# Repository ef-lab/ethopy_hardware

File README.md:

# 🏠 Hardware for EthoPy

Welcome to the **Hardware for EthoPy** repository! This collection includes all hardware information required to build the setups described in EthoPy. 

## 📦 What's Inside

This repo includes one folder for each behavioral system supported by EthoPy with the:
- **Instructions** – step-by-step guides to build this setup and parts list 
- **Figures** - Photos illustrating the construction process and final setup
- **3d_designs** – ready-to-print `.stl` files 

## 📁 File Structure

```bash
├── Air-track
│   ├── 3d_designs
│   ├── Air-track_instructions.md
│   └── figures
├── EthoPy_Controller
│   ├── Controller_Figures
│   ├── EthoPy_Controller_Board.md
│   ├── EthoPy_Controller_code.ino
│   ├── Lick_Valves_final.jpg
│   ├── Lick_Valves_final.kicad_pcb
│   ├── Valve_Controller.pdf
│   └── gerbers
├── Homecage
│   ├── 3d_designs
│   ├── Lick_ports_Figures
│   ├── Lick_ports_assemply.md
│   ├── RP_Figures
│   ├── RP_instructions.md
│   ├── Speakers_Figures
│   └── Speakers_assemply.md
├── LICENSE
├── Open-field
│   ├── 3d_designs
│   ├── Open-field_Figures
│   └── Open-field_instructions.md
├── README.md
└── Spherical_Treadmill
    ├── 3d_design
    ├── figures
    └── spherical_treadmill_instructions.md
```

<!-- ## 📸 Gallery

_Add screenshots or photos of the final printed setup here!_ -->

## 🛠️ Modifications & Contributions

Want to tweak a design? Feel free to fork the repo and customize. PRs are welcome if you want to contribute new variations or improvements!

## 📜 License

This project is licensed under the **MIT License** – see the [LICENSE](./LICENSE) file for details.

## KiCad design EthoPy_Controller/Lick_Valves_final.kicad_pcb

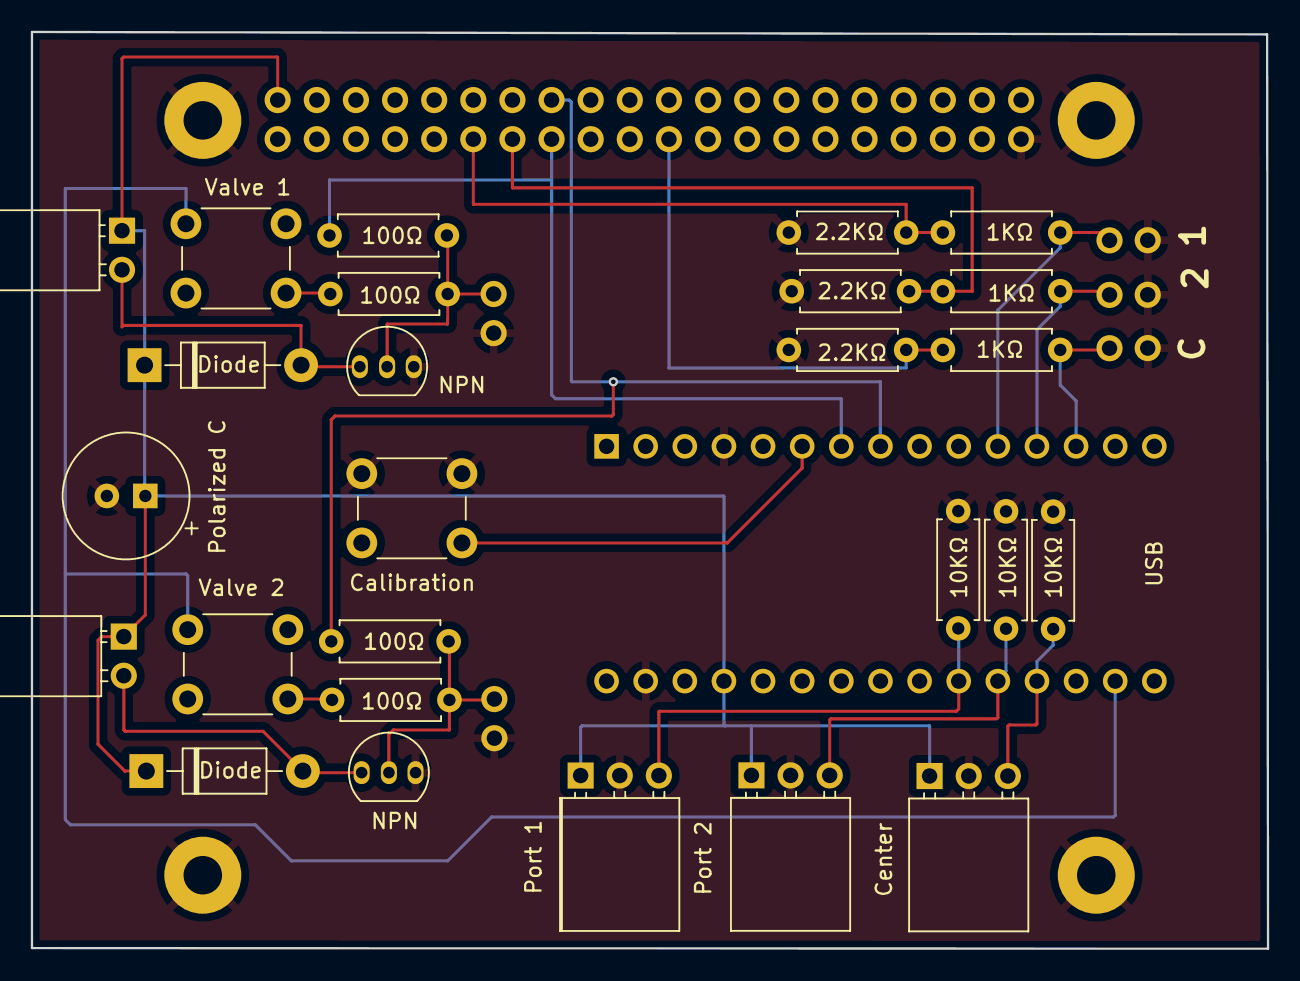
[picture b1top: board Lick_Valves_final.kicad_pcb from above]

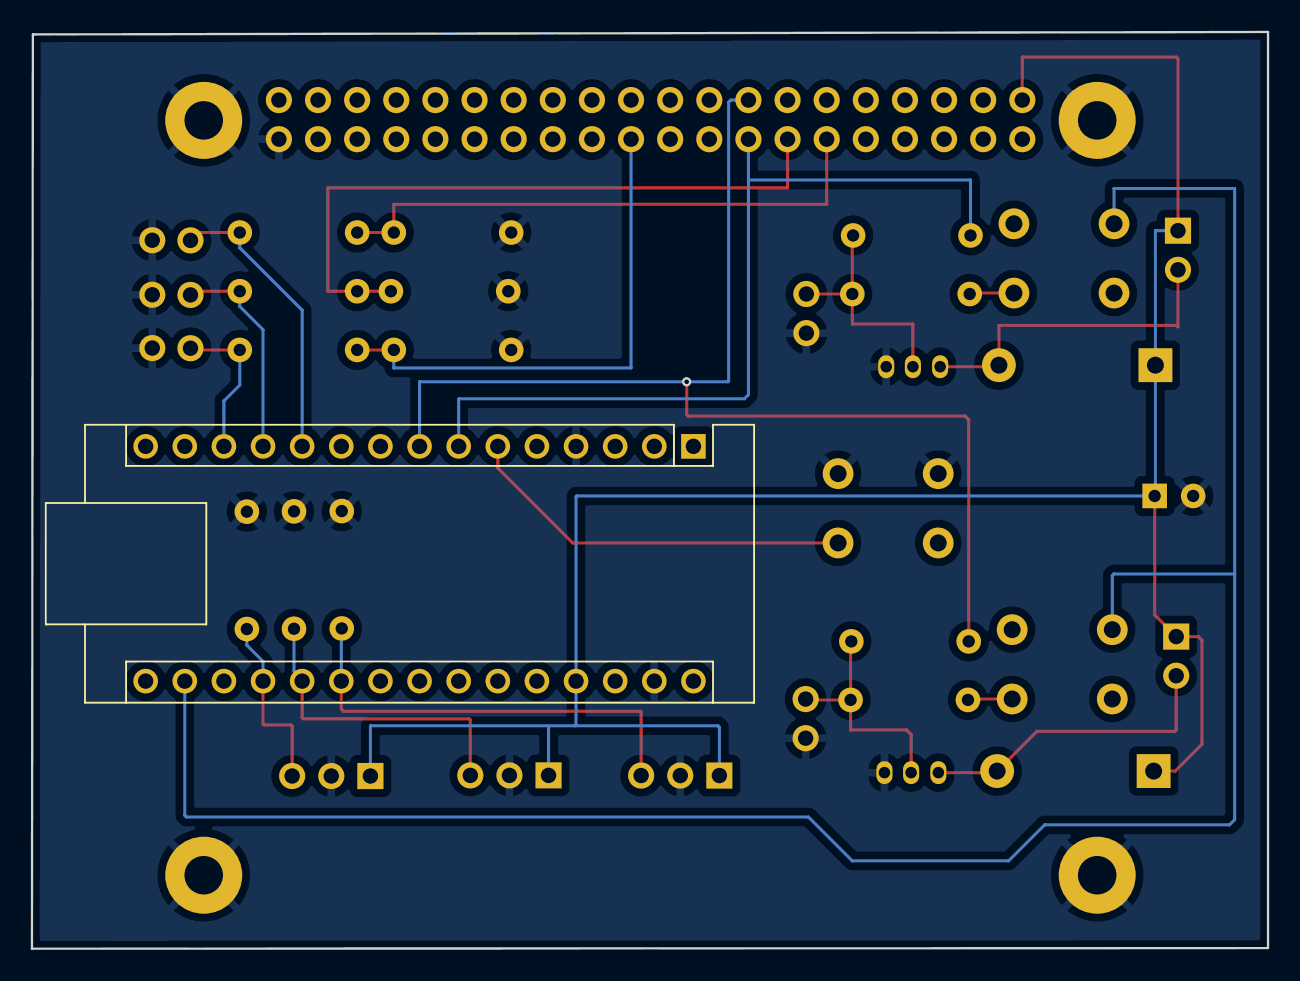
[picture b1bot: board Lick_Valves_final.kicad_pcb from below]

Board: 4 copper layers, 80.2 x 59.5 mm, 32 parts (2 on the bottom side), 21 nets.

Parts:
A1: Arduino_Nano_Every; Arduino_Nano
C1: C_Polarized; CP_Radial_D8.0mm_P2.50mm
D1, D3: 4.7V; D_DO-41_SOD81_P10.16mm_Horizontal
J1, J2: Conn_01x02_Pin; PinSocket_1x02_P2.54mm_Horizontal
J3, J10: Conn_01x03_Pin; PinHeader_1x03_P2.54mm_Vertical
J4, J5, J6: Conn_01x03_Pin; PinSocket_1x03_P2.54mm_Horizontal
J7, J9: Conn_01x02_Pin; PinHeader_1x02_P2.54mm_Vertical
J8: Conn_02x20_Odd_Even; PinSocket_2x20_P2.54mm_Vertical
Q1, Q3: BC547; TO-92_Inline
R1, R2, R3, R10: 100Ω; R_Axial_DIN0207_L6.3mm_D2.5mm_P7.62mm_Horizontal
R4, R6, R8: 1kΩ; R_Axial_DIN0207_L6.3mm_D2.5mm_P7.62mm_Horizontal
R5, R7, R9: 2.2ΚΩ; R_Axial_DIN0207_L6.3mm_D2.5mm_P7.62mm_Horizontal
R11: 10kΩ; R_Axial_DIN0207_L6.3mm_D2.5mm_P7.62mm_Horizontal
R12, R13: 10ΚΩ; R_Axial_DIN0207_L6.3mm_D2.5mm_P7.62mm_Horizontal
SW1, SW2: SW_Push; SW_PUSH_6mm
SW3: Calibration; SW_PUSH_6mm

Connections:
+3.3V: A1.17 (3V3), SW1.1, SW2.1
+5V: A1.27 (+5V), C1.1, D1.1 (K), D3.1 (K), J1.1, J2.1, J4.1, J5.1, J6.1, J8.2
GND: A1.4 (GND), A1.29 (GND), C1.2, J4.2, J5.2, J6.2, J7.1, J8.39, J9.1, J10.1, J10.2, J10.3, Q1.3 (E), Q3.3 (E), R5.1, R7.1, R9.1, R11.1, R12.1, R13.1, SW3.1
unnamed: A1.19 (A0), J5.3, R11.2
unnamed: A1.20 (A1), J4.3, R12.2
unnamed: A1.21 (A2), J6.3, R13.2
unnamed: A1.6 (D3), SW3.2
unnamed: A1.7 (D4), J8.15, R3.1
unnamed: A1.8 (D5), J8.16, R2.1
unnamed: A1.11 (D8), J3.1, R4.2
unnamed: A1.12 (D9), J3.2, R6.2
unnamed: A1.13 (D10), J3.3, R8.2
unnamed: D1.2 (A), J2.2, Q1.1 (C)
unnamed: D3.2 (A), J1.2, Q3.1 (C)
unnamed: J8.11, R4.1, R5.2
unnamed: J8.13, R6.1, R7.2
unnamed: J8.21, R8.1, R9.2
unnamed: J9.2, Q1.2 (B), R2.2, R10.1
unnamed: J7.2, Q3.2 (B), R1.1, R3.2
unnamed: R1.2, SW1.2
unnamed: R10.2, SW2.2

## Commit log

2025-04-16 add 3d designs for homecage setup
2025-04-16 add readme and info .md files
2025-06-10 update folder structure and add VR files
2025-06-10 edit VR_assembly.md
2025-06-10 edit VR_assembly.md and add pictures
2025-06-10 modify images
2025-06-10 modify parts list
2025-07-21 add board pdf test
2025-07-21 upload pdfs fot homecage
2025-07-21 upload pdfs fot homecage and delete old files
2025-07-21 update folder name
2025-07-21 add air-trck files
2025-07-21 add openfield files
2025-07-21 remove vr
2025-07-21 add ehtopy controller design files and code
2025-07-30 Convert air-track setup PDF to Markdown
2025-07-30 fix fig refs and modify notes
2025-07-30 small adjustments
2025-07-30 docs: add RP_instructions.md
2025-07-31 Upload markdown file for Homecage hardware
2025-07-31 Style: Update md & add hyperlinks
2025-07-31 Update style & Hardware tables (Sources/Identifiers)
2025-07-31 remove ethopy_controller from homecage
2025-07-31 remove again
2025-07-31 Upload markdown file for Open-field hardware
2025-07-31 Upload Ball hardware
2025-08-04 rename Ball to Spherical_Treadmill
2025-08-04 update link (RP_instructions) & figure7 (Speakers)
2025-08-04 fix/feat: activate links; add figures; Update tree view in README.md
2026-02-19 docs(readme): include pricing information
2026-02-20 doc: update prices
